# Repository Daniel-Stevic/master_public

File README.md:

# master_public
Master's Thesis Work of Daniel Stević
Thesis Text can be found at https://epub.technikum-wien.at/ with the Name:
'Untersuchung zweier zweistufiger verschachtelter nichtinvertierender schwebender Hochsetzsteller Topologien vierter Ordnung'

----------------------------------------------------------------------------------------------------

Licenses CC_by-nc_4.0 applies to all provided data.

Acknowledgement and References:

The schematic drawings and signal diagrams in the 'Pictures_and_Graphics' directory were created using Inkscape v1.4.2.
The symbols were created using the openly available Inkscape library provided by the 
Department of Power Electronics and Electrical Drives at Paderborn University - LEA and can be found here:
https://github.com/upb-lea/Inkscape_electric_Symbols

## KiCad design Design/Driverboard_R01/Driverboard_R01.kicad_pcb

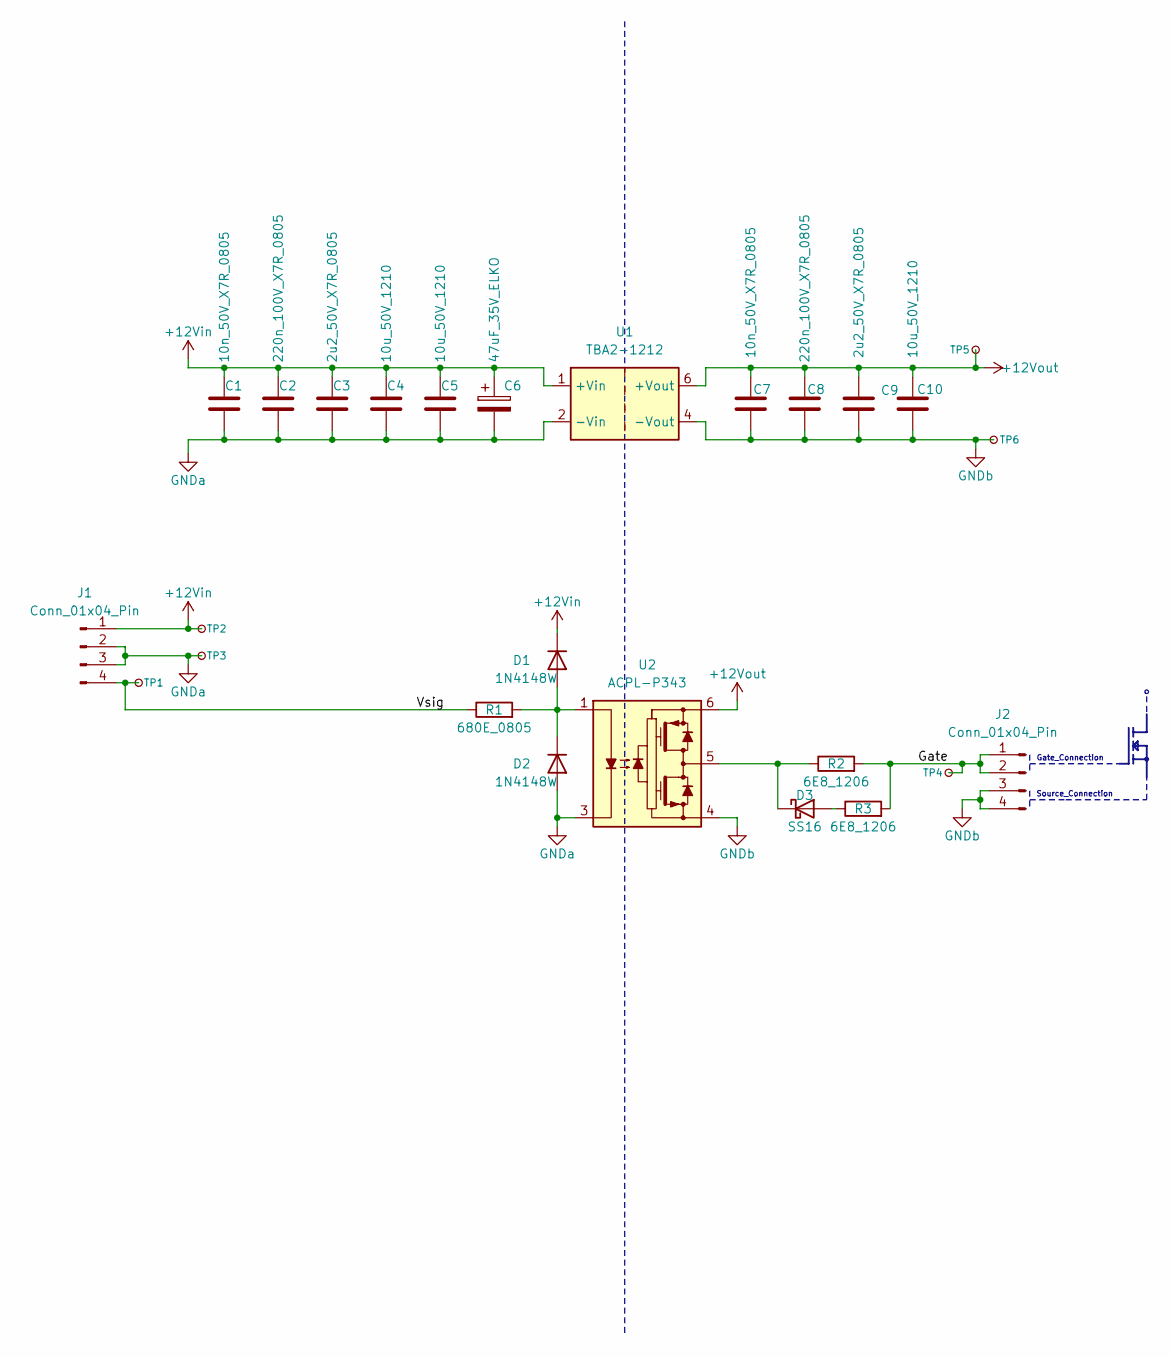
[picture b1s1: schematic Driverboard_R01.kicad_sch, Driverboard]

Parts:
C1, C7: 10n_50V_X7R_0805; C_0805_2012Metric; MPN C0805C103K5RAC7210
C2, C8: 220n_100V_X7R_0805; C_0805_2012Metric; MPN GRM21AR72A224KAC5K
C3, C9: 2u2_50V_X7R_0805; C_0805_2012Metric; MPN CL21B225KBYNNWE
C4, C5, C10: 10u_50V_1210; C_1210_3225Metric; MPN GCM32EC71H106KA03L
C6: 47uF_35V_ELKO; CP_Elec_6.3x5.7; MPN A768EB476M1VLAE042
D1, D2: 1N4148W; D_SOD-123; MPN 1N4148W-13-F
D3: SS16; SS12FP; MPN SS16FP
J1, J2: Conn_01x04_Pin; PinHeader_1x04_P2.54mm_Vertical; MPN NotPlaced
R1: 680E_0805; R_0805_2012Metric; MPN RC0805FR-07680RL
R2, R3: 6E8_1206; R_1206_3216Metric; MPN RC1206JR-076R8L
TP1, TP2, TP3, TP4, TP5, TP6: TestPoint_Small; TestPoint_Pad_D1.0mm; MPN NotPlaced
U1: TBA2-1212; Converter_DCDC_TRACO_TBA2-1212_Single_THT; MPN TBA2-1212
U2: ACPL-P343; SSO-6_6.8x4.6mm_P1.27mm_Clearance7mm; MPN ACPL-P345-000E

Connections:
+12Vin: C1.1, C2.1, C3.1, C4.1, C5.1, C6.1, D1.1 (K), J1.1, TP2.1, U1.1 (+Vin)
+12Vout: C7.1, C8.1, C9.1, C10.1, TP5.1, U1.6 (+Vout), U2.6 (VCC)
/Gate: J2.1, J2.2, R2.2, R3.2, TP4.1
/Vsig: J1.4, R1.1, TP1.1
GNDa: C1.2, C2.2, C3.2, C4.2, C5.2, C6.2, D2.2 (A), J1.2, J1.3, TP3.1, U1.2 (-Vin), U2.3 (C)
GNDb: C7.2, C8.2, C9.2, C10.2, J2.3, J2.4, TP6.1, U1.4 (-Vout), U2.4 (VEE)
unnamed: D1.2 (A), D2.1 (K), R1.2, U2.1 (A)
unnamed: D3.2 (A), R3.1
unnamed: D3.1 (K), R2.1, U2.5 (VO)

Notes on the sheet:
Gate_Connection
Source_Connection

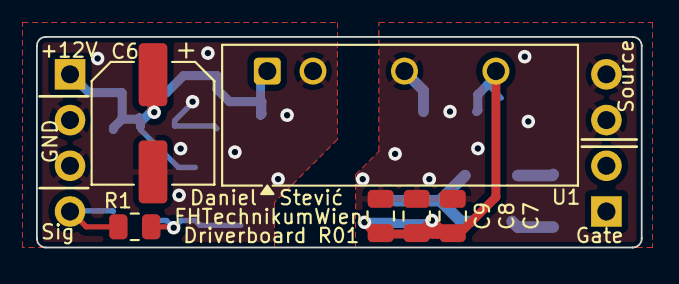
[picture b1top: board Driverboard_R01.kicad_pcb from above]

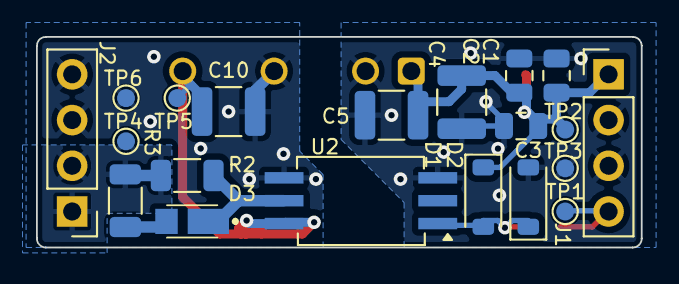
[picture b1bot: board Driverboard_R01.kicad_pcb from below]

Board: 2 copper layers, 33.6 x 11.7 mm, 26 parts (20 on the bottom side), 9 nets.

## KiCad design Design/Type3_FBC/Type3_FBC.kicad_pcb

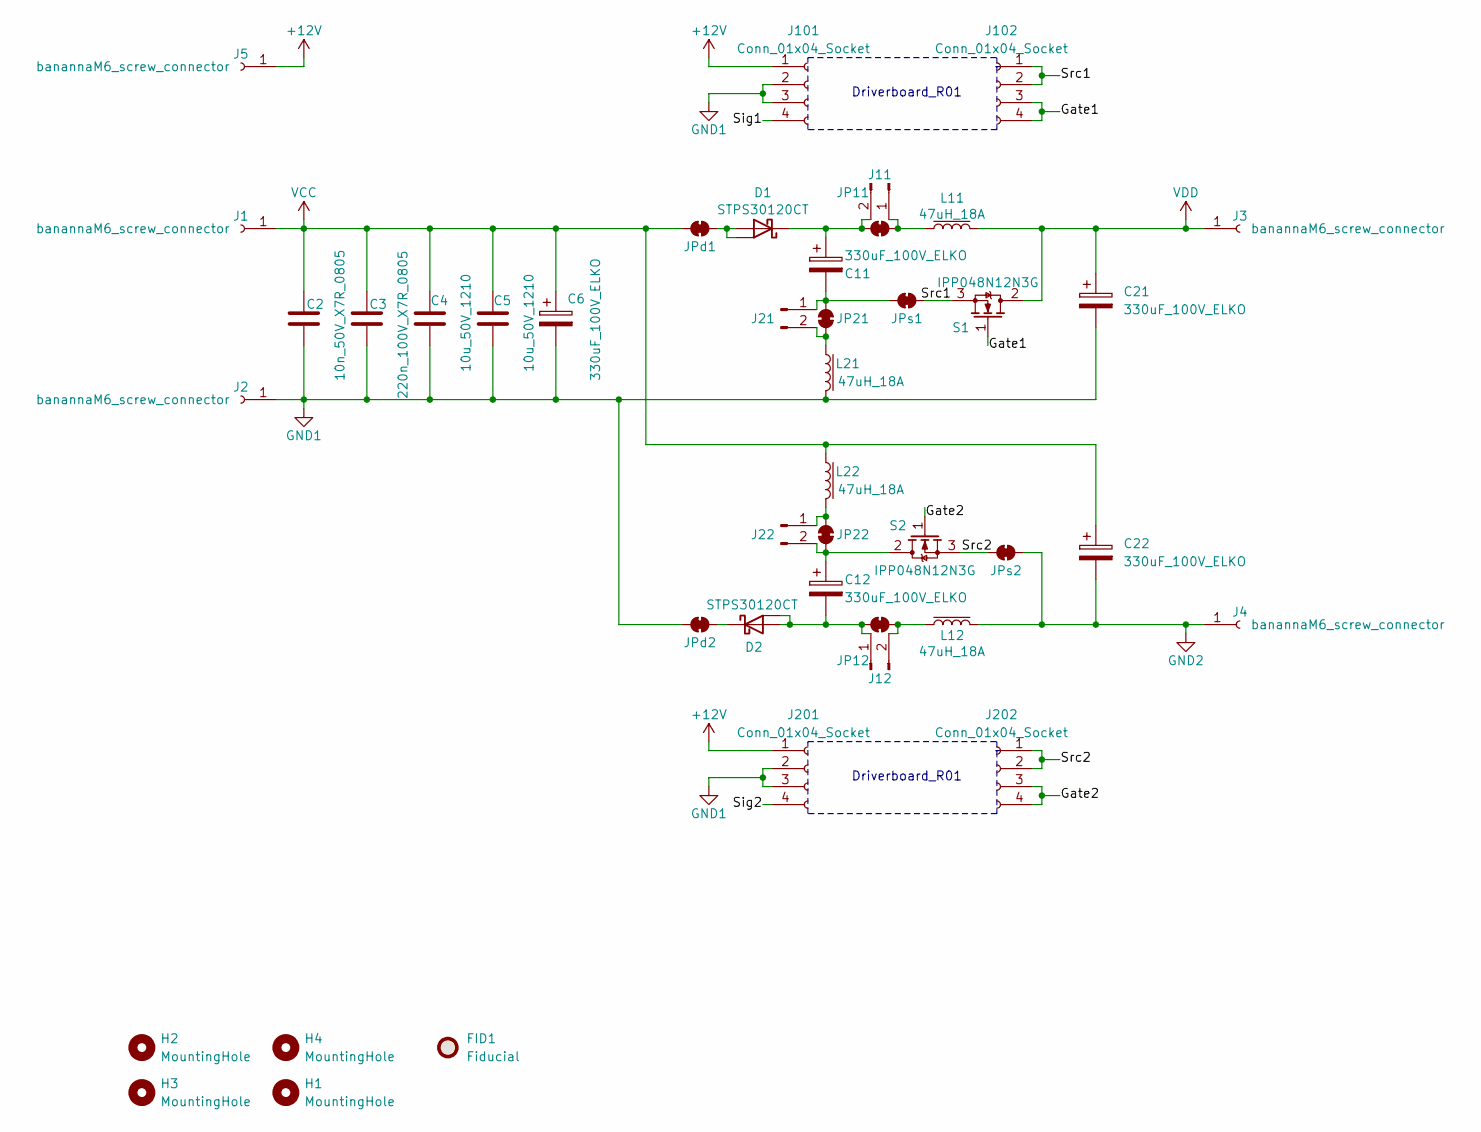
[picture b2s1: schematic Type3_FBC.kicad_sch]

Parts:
C2: 10n_50V_X7R_0805; C_0805_2012Metric; MPN C0805C103K5RAC7210
C3: 220n_100V_X7R_0805; C_0805_2012Metric; MPN GRM21AR72A224KAC5K
C4, C5: 10u_50V_1210; C_1210_3225Metric; MPN GCM32EC71H106KA03L
C6, C11, C12, C21, C22: 330uF_100V_ELKO; CP_Radial_D16.0mm_P7.50mm; MPN UPS2A331MHD1TN
D1, D2: STPS30120CT; TO-220-3_Vertical; MPN STPS30120CT
FID1: Fiducial; Fiducial_0.5mm_Mask1mm; MPN NotPlaced
H1, H2, H3, H4: MountingHole; MountingHole_3.2mm_M3; MPN NotPlaced
J1, J2, J3, J4, J5: banannaM6_screw_connector; bannana_M6_screw_connector; MPN NotPlaced
J11, J12, J21, J22: Conn_01x02_Pin; PhoenixContact_MCV_1,5_2-G-3.5_1x02_P3.50mm_Vertical; MPN 1843606+1830715
J101, J102, J201, J202: Conn_01x04_Socket; PinSocket_1x04_P2.54mm_Vertical; MPN 5-146763-6
JP11, JP12, JP21, JP22: SolderJumper_2_Bridged_small; SolderJumper2_1.0x3mm_0.3mm; MPN NotPlaced
JPd1, JPd2: SolderJumper_2_Bridged_small; SolderJumper2_1.0x3mm_0.3mm; MPN NotPlaced
JPs1, JPs2: SolderJumper_2_Bridged_small; SolderJumper2_1.0x3mm_0.3mm; MPN NotPlaced
L11, L12, L21, L22: 47uH_18A; AGP4233473ME; MPN AGP4233-473ME
S1, S2: IPP048N12N3G; TO-220-3_Vertical; MPN IPP048N12N3G

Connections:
+12V: J5.1, J101.1, J201.1
/Gate1: J102.3, J102.4, S1.1 (GN)
/Gate2: J202.3, J202.4, S2.1 (GN)
/Sig1: J101.4
/Sig2: J201.4
/Src1: J102.1, J102.2, JPs1.2 (B), S1.3 (SN)
/Src2: J202.1, J202.2, JPs2.1 (A), S2.3 (SN)
GND1: C2.2, C3.2, C4.2, C5.2, C6.2, C21.2, J2.1, J101.2, J101.3, J201.2, J201.3, JPd2.1 (A), L21.2
GND2: C22.2, J4.1, JPs2.2 (B), L12.2
unnamed: D1.1 (A1), D1.3 (A2), JPd1.2 (B)
unnamed: C11.1, D1.2 (K), J11.2, JP11.2 (B)
unnamed: C12.2, D2.1 (A1), D2.3 (A2), J12.1, JP12.2 (B)
unnamed: D2.2 (K), JPd2.2 (B)
unnamed: J11.1, JP11.1 (A), L11.1
unnamed: J12.2, JP12.1 (A), L12.1
unnamed: C11.2, J21.1, JP21.2 (B), JPs1.1 (A)
unnamed: J21.2, JP21.1 (A), L21.1
unnamed: J22.1, JP22.2 (B), L22.2
unnamed: C12.1, J22.2, JP22.1 (A), S2.2 (DN)
VCC: C2.1, C3.1, C4.1, C5.1, C6.1, C22.1, J1.1, JPd1.1 (A), L22.1
VDD: C21.1, J3.1, L11.2, S1.2 (DN)

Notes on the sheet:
Driverboard_R01

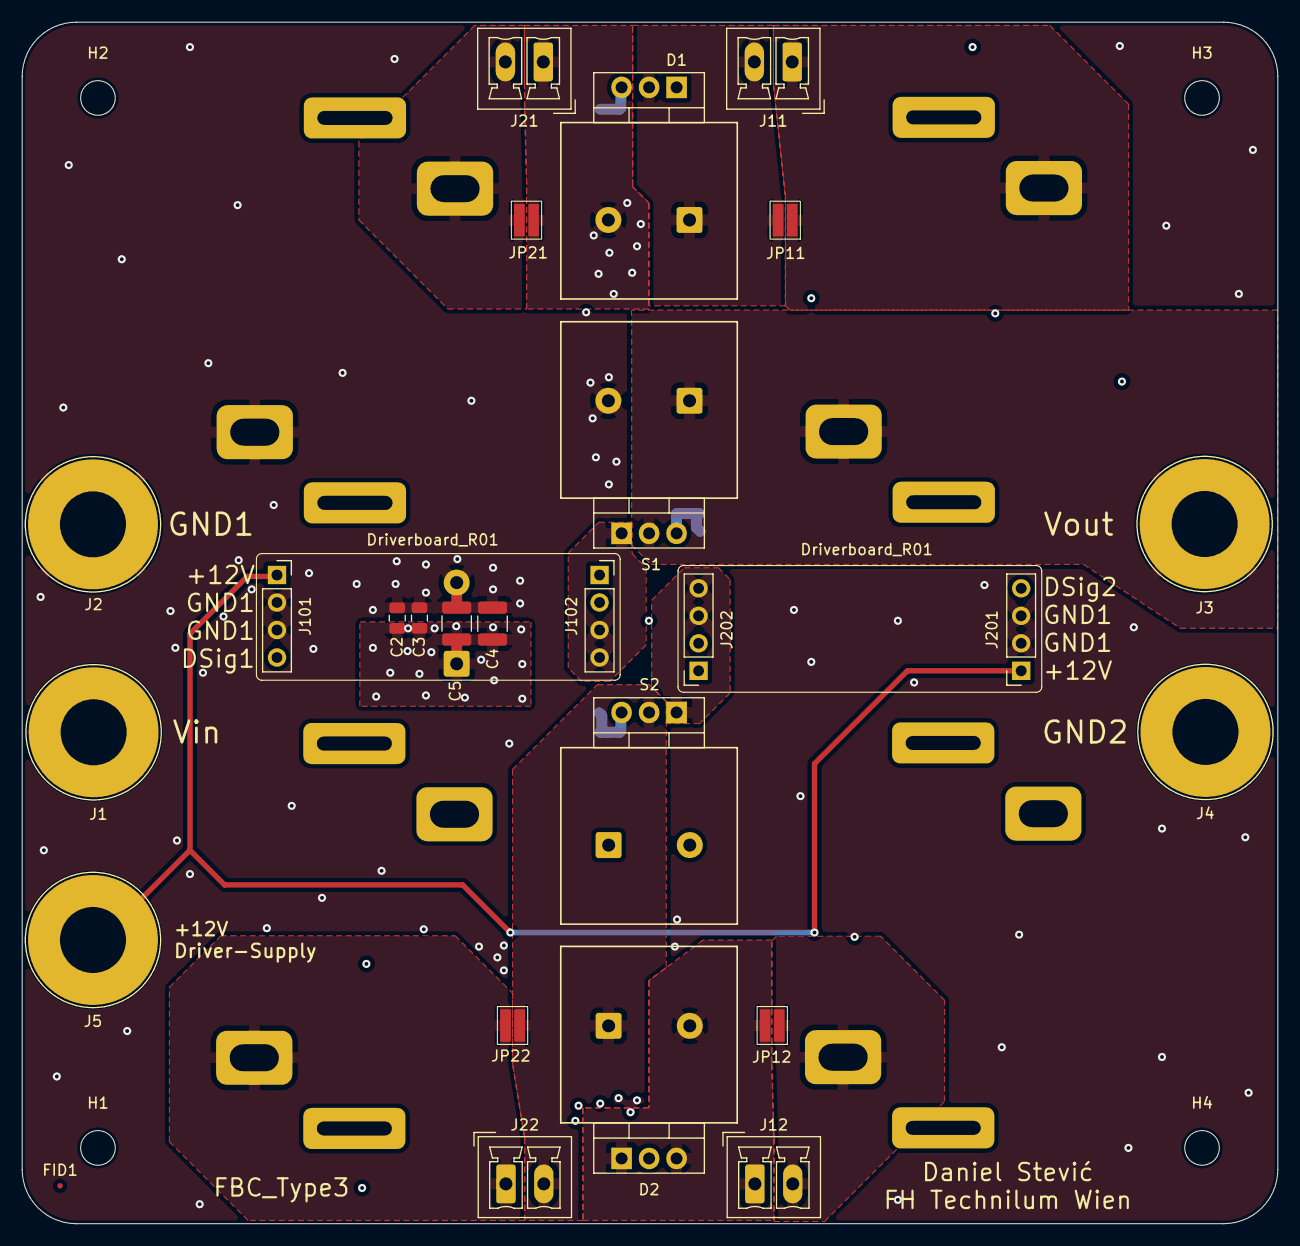
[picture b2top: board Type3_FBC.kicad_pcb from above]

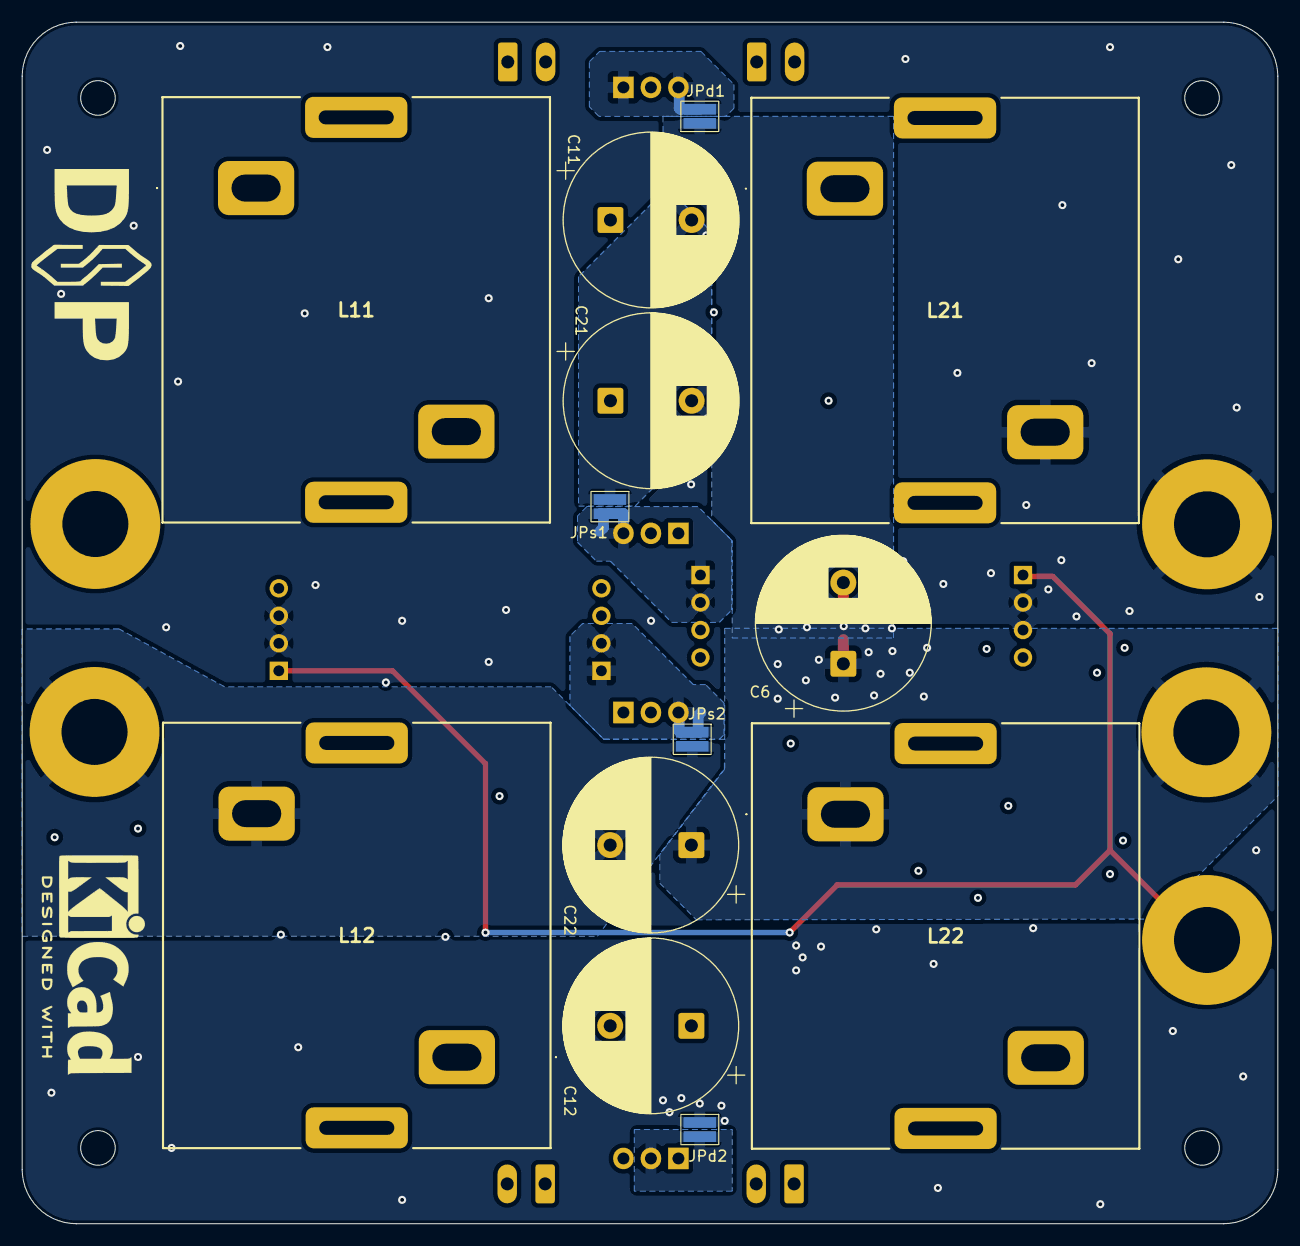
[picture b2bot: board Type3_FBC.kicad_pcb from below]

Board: 4 copper layers, 116.0 x 111.0 mm, 43 parts (13 on the bottom side), 19 nets.
